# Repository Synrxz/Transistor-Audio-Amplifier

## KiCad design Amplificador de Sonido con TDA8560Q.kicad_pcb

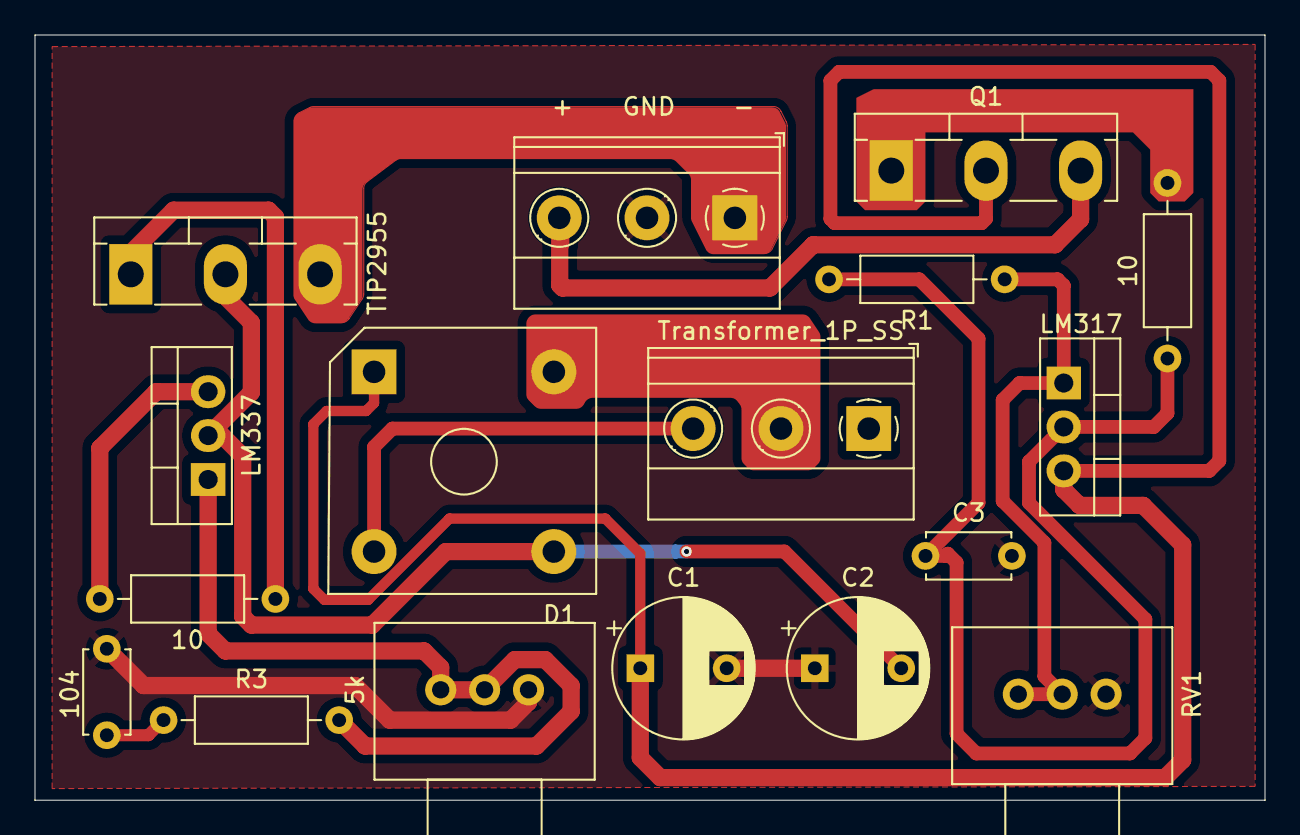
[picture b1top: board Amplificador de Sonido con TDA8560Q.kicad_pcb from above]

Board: 2 copper layers, 71.2 x 44.3 mm, 17 parts (0 on the bottom side), 12 nets.

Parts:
C1, C2: 4700uF; CP_Radial_D8.0mm_P5.00mm
C3, C4: 104; C_Disc_D4.7mm_W2.5mm_P5.00mm
D1: Diode Bridge; Diode_Bridge_Vishay_KBPC6
J2: Screw_Terminal_01x03; TerminalBlock_Phoenix_MKDS-1,5-3-5.08_1x03_P5.08mm_Horizont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
Q1: TIP3055; TO-218-3_Vertical
Q2: TIP2955; TO-218-3_Vertical
R1, R3: 240; R_Axial_DIN0207_L6.3mm_D2.5mm_P10.16mm_Horizontal
R2, R4: 10; R_Axial_DIN0207_L6.3mm_D2.5mm_P10.16mm_Horizontal
RV1, RV2: 5k; Potentiometer_Vishay_148-149_Single_Horizontal
T1: Transformer_1P_SS; TerminalBlock_Phoenix_MKDS-1,5-3-5.08_1x03_P5.08mm_Horizont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
U1: LM317; TO-220-3_Vertical
U3: LM337; TO-220-3_Vertical

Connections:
/OUT -: J2.3, Q2.3 (E)
/OUT+: J2.1, Q1.3 (E)
GND: C1.2, C2.1, C3.2, C4.2, J2.2, RV1.3, RV2.3
unnamed: C1.1, D1.1 (+), Q1.2 (C), U1.3 (VI)
unnamed: C2.2, D1.3 (-), Q2.2 (C), U3.2 (VI)
unnamed: Q1.1 (B), R2.2
unnamed: Q2.1 (B), R4.2
unnamed: D1.2, T1.3 (SA)
unnamed: R1.1, RV1.1, RV1.2, U1.1 (ADJ)
unnamed: C3.1, R1.2, R2.1, U1.2 (VO)
unnamed: R3.2, RV2.1, RV2.2, U3.1 (ADJ)
unnamed: C4.1, R3.1, R4.1, U3.3 (VO)

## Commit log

2024-12-02 Rename Imagen de WhatsApp 2024-12-02 a las 11.05.39_28173ae1.jpg to Diagram
2024-12-02 Rename Imagen de WhatsApp 2024-12-02 a las 11.05.40_3ad3f4be.jpg to 3D View
